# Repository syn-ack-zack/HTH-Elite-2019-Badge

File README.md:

# Hackers Teaching Hackers 2019 Badge
This repository contains the hardware and software source code to fabrciate the HTH 2019 Badge. Details on the use and flashing of the badge can be found below. 

## Badge Hardware Specs
* ESP32
* Atmel 32u4
* 96×64 Graphic Full Color OLED Display
* 19x Mini NeoPixel RGB LEDs
* 4 tactile buttons
* 8 Mb Storage
* 1 2x3 "Shitty Add On" Connector
* Powered via 2 AA batteries or USB

## Badge Functions
* LoRa Arsenal
	* LoRa 915Mhz Tactile Button Chat
	* LoRa 915Mhz Web App Chatroom
* WiFi Tools
	* 802.11 channel activity monitor
	* Access point scanner / Open AP detector
	* Packet Monitor and Deauth sniffer
	* Can act as a client or access point (modify config.json via SPIFFS to update AP connection details)
	* Webserver (edit filesystem files, trigger payloads remotely)
	* NTP client
* HID Toolkit (Not Working)
	* An issue with the serial communication currently prevents the ESP32 from controlling the Atmega. 
	* Any HID functionality must be standalone and flashed to the Atmega.
	* This repo will be updated as any changes occur.
	
* LED patterns and OLED graphics
* Misc. extras

## Usage Instructions
### Power Switch
In order to turn on the device, it must be powered via 2 AA batteries or USB. The main power switch is located in the center.

### Buttons / UI

Up and Down is on the left side of the OLED, and Left and Right is on the right side of the OLED.

In order to go into a menu or run a program, click the right button. To exit most applications, click the left button. Some programs like the snake game require all 4 buttons so there is no way to clean exit, a power cycle is needed. 

### HTH NET (LoRa 915Mhz)
This badge contains an SX1278 LoRa transceiver which allows for long range low bandwidth communication using the LoRa protocol over 915Mhz. Each badge is capable of receiving and sending messages using this frequency by utilizing the HTH NET feature of the badge. 

Once you start the chat it will display any received message on the screen. Follow the on screen prompts to type out and send messages. The '~' is used as a delimiter to signify the end of a typed message. 

Alternatively you can utililze the Webserver by first starting up the Access Point at `WiFi Server Tools -> AP Start`. Connect to this network and then start up the Webserver at `WiFi Server Tools -> Webserver Start`. Navigate to the indicated IP, http://10.0.1.5/ to access the web app. HTH Net can be utilized here to have a more convenient interface to send and recieve LoRa messages. 

### Webserver
Navigate to WiFi Server Tools -> Webserver Start. You can access the webserver if running an AP or if connected. The pages are protected through basic authentication, username and password generated dynamically and is provided on the screen.

A SPIFFS Editor can be used to edit the flash filesystem on the badge. This is useful to modify config files which are used in several instances. For instance, to have your badge connect to another wireless network, you configure the ESSID and Password in `config.json`. 

### Bling
There are 40+ LED patterns included. You can also trigger each type of pattern individually. 

## Configuration / Customization
### Settings menu in OLED UI
There are individual settings for OLED and LED brightness. Region setting is related to WiFi channel scanning.

### JSON configuration files
There are 4 different json files in SPIFFS. There are a couple ways to edit these files and get them loaded on the badge, but the easiest is through the webserver.
1. config.json = Main device configuration. Includes parameters such as LED and OLED brightness settings, ssid/password if connecting to a wireless client network, region information, and google auth HMAC. 
2. lin.json / win.json = Configuration files for the Linux and Windows KB/M payloads. 
3. static.json = Configuration file for the stored static strings. 

## Compiling Instructions
These instructions will get you a copy of the project up and running on your local machine.
### Prerequisites
What things you need to install the software and how to install them
```
1. Arduino / compiler
2. SparkFun Pro Micro v3 com driver
https://learn.sparkfun.com/tutorials/pro-micro--fio-v3-hookup-guide/installing-windows
https://learn.sparkfun.com/tutorials/pro-micro--fio-v3-hookup-guide/installing-mac--linux
3. Libraries
  https://raw.githubusercontent.com/sparkfun/Arduino_Boards/master/IDE_Board_Manager/package_sparkfun_index.json
  https://github.com/adafruit/Adafruit_NeoPixel
  https://github.com/adafruit/Adafruit-GFX-Library
  https://github.com/adafruit/Adafruit_CircuitPlayground
  https://github.com/kitesurfer1404/WS2812FX
  https://github.com/me-no-dev/ESPAsyncWebServer
  https://github.com/me-no-dev/AsyncTCP
  https://github.com/bblanchon/ArduinoJson
  https://github.com/me-no-dev/arduino-esp32fs-plugin
  https://github.com/sandeepmistry/arduino-LoRa
  Manually copy the SSD_13XX and qMenuSystem folders to Arduino libraries folder. We included a snapshot of the other libraries used in case newer versions break our code.
4. 3.3v FTDI serial cable
5. Hackers Teaching Hackers 2019 Badge
```
### Compiling / Flashing Atmel Code
* Set the board to SparkFun Pro Micro
* Set the processor as ATmega32u4 3.3v and NOT the 5v one

### Compiling / Flashing ESP Code
* Set the board to SparkFun ESP32 Thing

#### Programming through FTDI port 
To interface with the ESP32 over FTDI serial, you will need a FTDI USB adapter. These can be found online or at some retailers like MicroCenter. [FTDI Adapter on Amazon](https://www.amazon.com/HiLetgo-FT232RL-Converter-Adapter-Breakout/dp/B00IJXZQ7C/ref=pd_lpo_sbs_147_t_1?_encoding=UTF8&psc=1&refRID=TW098QMMC5YX7B7DFNS5)

1. Flash the atmel with the 'atmel-esp32ftdi-pin7' code first via the USB connection. this will toggle pin 7 and the rx/tx switch to change the serial port communiction to the FTDI port. 
2. Connect FTDI cable to the board while holding the left button down (which is on the right side, top button)
3. Upload code.
4. You can optionally flash the 'atmel-km-relay' code back to the atmel. Most serial functionality isn't working correctly at this time, however the mouse jiggler feature is configured to work when plugged in. Note that you may need to reset the the atmel by shorting GND to [Pin 13](https://www.arduino.cc/en/Hacking/PinMapping32u4) before succesfully reflashing. 

#### Programming through USB port / Atmel
Pass through programming doesn't work at the time of writing. Communication is passed through, but something is holding up the ESP32 from fully going into the programming mode

### Uploading SPIFFS files
The keyboard/mouse payloads, configuration files, webserver files are all files that are loaded into a special section in storage marked as SPIFFS. While still having pin 7 set to allow for the FTDI connection, use the 'ESP32 Sketch Data Upload' function in the tools menu. This will compress and compile all the files in the 'data' folder, and upload it. 

## Authors / Contributors
* **@syn-ack-zack**

## Acknowledgments
* Thanks to all contributes and maintainers of any codebase which was used or referenced. 
* Special thanks to Hacker Warehouse and Garret Gee for the work on their [DC26 badge](https://github.com/hackerwarehouse/HW-DC26-Badge). Much of the materials around the core components (esp32 / atmega34u ) was referenced from Hacker Warehouse's open sourced badge.

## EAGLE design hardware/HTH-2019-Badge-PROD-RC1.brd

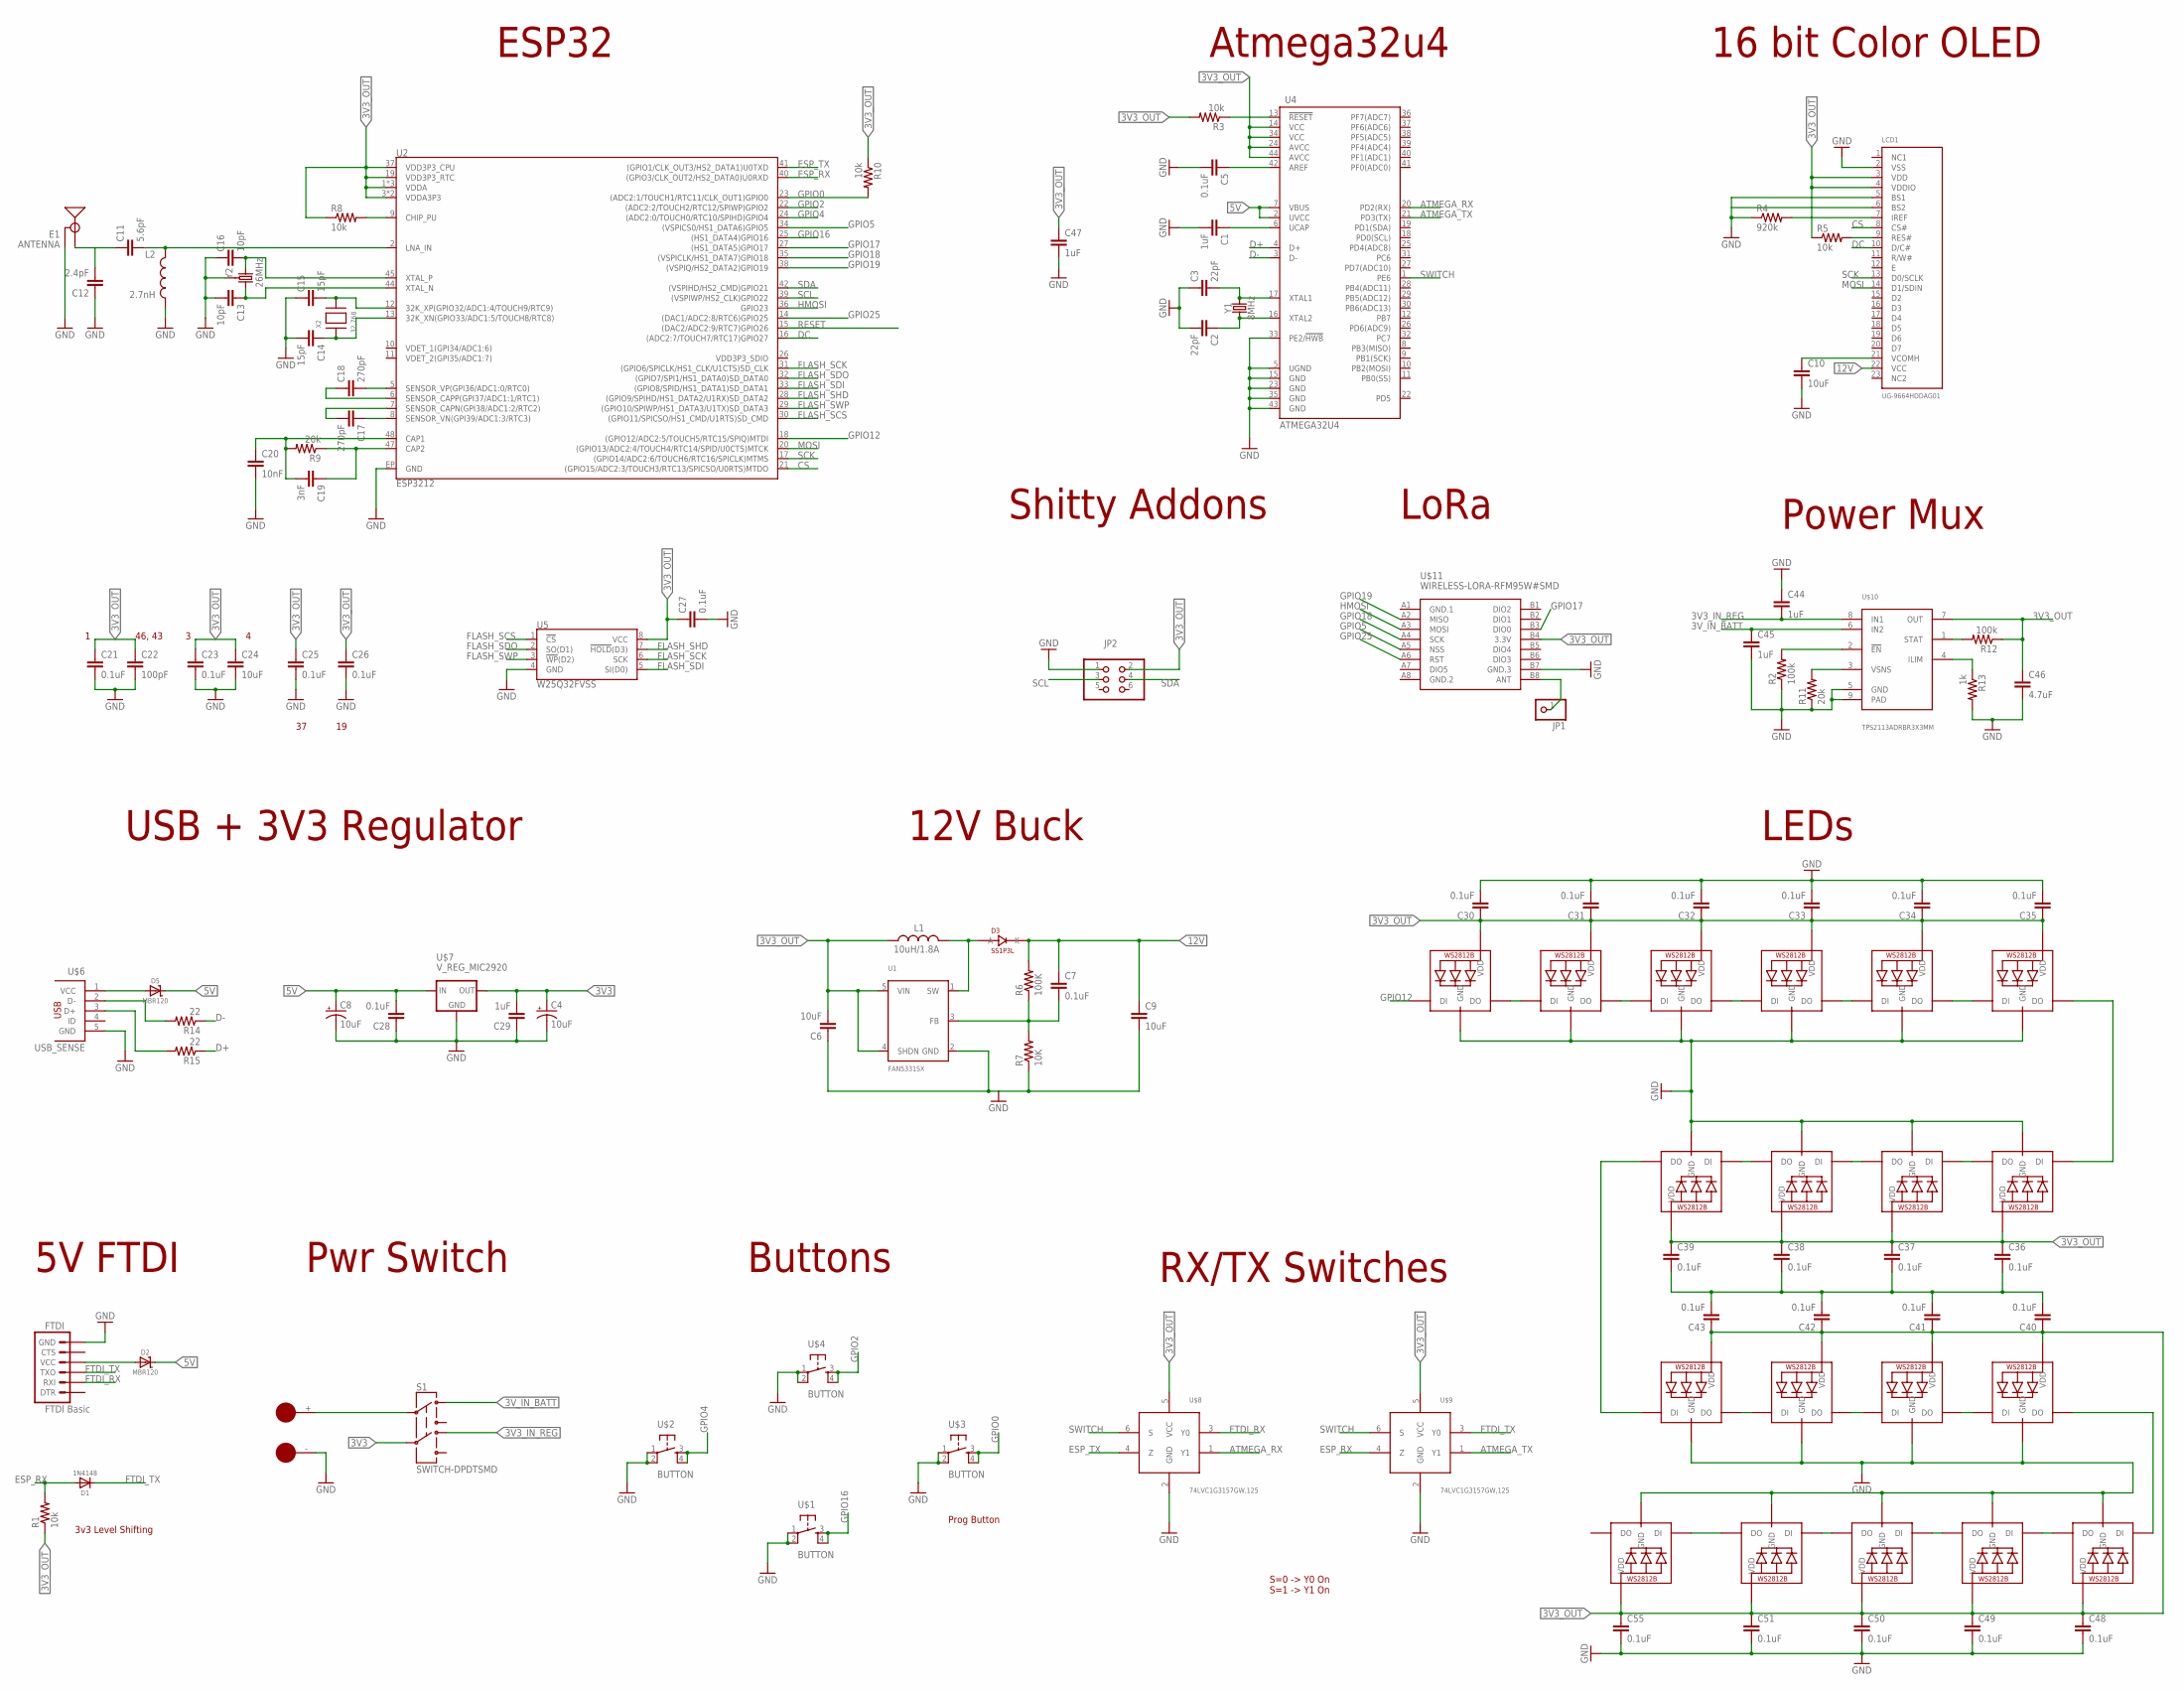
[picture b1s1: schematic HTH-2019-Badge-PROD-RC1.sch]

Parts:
C1, C29, C44, C45, C47: 1uF; CAP0603
C2, C3: 22pF; CAP0603
C4, C8: 10uF; EIA3216
C5, C7, C21, C23, C25, C26, C27, C28, C30, C31, C32, C33, C34, C35, C36, C37, C38, C39, C40, C41, C42, C43, C48, C49, C50, C51, C55: 0.1uF; CAP0603
C6, C9, C10, C24: 10uF; CAP0603
C11: 5.6pF; CAP0603
C12: 2.4pF; CAP0603
C13, C16: 10pF; CAP0603
C14, C15: 15pF; CAP0603
C17, C18: 270pF; CAP0603
C19: 3nF; CAP0603
C20: 10nF; CAP0603
C22: 100pF; CAP0603
C46: 4.7uF; CAP0603
D1: 1N4148; SOD-323
D2, D5: MBR120; SOD-123
D3: SS1P3L; DO220AAL
E1: ANTENNA; TRACE_ANTENNA_2.4GHZ_25.7MM_TUNED
FTDI: FTDI Basic; 1X06
JP1: PINHD-1X1; 1X01
JP2: PINHD-2X3; 2X03
L1: 10uH/1.8A; SRU5028
L2: 2.7nH; 0603
LCD1: UG-9664HDDAG01; UG-9664HDDAG01_WRAPAROUND
LED1, LED2, LED3, LED4, LED5, LED6, LED7, LED8, LED9, LED10, LED11, LED12, LED13, LED14, LED15, LED16, LED17, LED18, LED19: WS2812B3535; LED3535
R1, R3, R5, R8, R10: 10k; RES-0603
R2, R12: 100k; RES-0603
R4: 920k; RES-0603
R6: 100K; RES-0603
R7: 10K; RES-0603
R9, R11: 20k; RES-0603
R13: 1k; RES-0603
R14, R15: 22; RES-0603
S1: SWITCH-DPDTSMD; AYZ0202
U1: FAN5331SX; SOT23-5
U2: ESP3212; QFN48-0.4MM
U4: ATMEGA32U4; QFN-44-NOPAD_1:1-OUTFAKES
U5: W25Q32FVSS; SOIC-8
U$1, U$2, U$3, U$4: BUTTON
U$5: BAT_HOLD; AA
U$6: USB_SENSE; USB-MICRO-TH-SUPPORT
U$7: V_REG_MIC2920; SOT223
U$8, U$9: 74LVC1G3157GW,125; SOT-363
U$10: TPS2113ADRBR3X3MM; 8-VDFN
U$11: WIRELESS-LORA-RFM95W#SMD
X2: 32.768; XTAL3215
Y1: 8MHz; CRYSTAL-SMD-5X3.2-4PAD
Y2: 26MHz; CRYSTAL-SMD-3.2X2.5

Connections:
3V3: C4.A (+), C29.2, S1.5, U$7.3 (OUT)
3V3_IN_REG: C44.2, S1.4, U$10.8 (IN1)
3V3_OUT: C6.2, C21.1, C22.1, C23.1, C24.1, C25.1, C26.1, C27.1, C30.1, C31.1, C32.1, C33.1, C34.1, C35.1, C36.1, C37.1, C38.1, C39.1, C40.1, C41.1, C42.1, C43.1, C46.1, C47.1, C48.1, C49.1, C50.1, C51.1, C55.1, JP2.2, L1.1, LCD1.3 (VDD), LCD1.4 (VDDIO), LED1.2 (VDD), LED2.2 (VDD), LED3.2 (VDD), LED4.2 (VDD), LED5.2 (VDD), LED6.2 (VDD), LED7.2 (VDD), LED8.2 (VDD), LED9.2 (VDD), LED10.2 (VDD), LED11.2 (VDD), LED12.2 (VDD), LED13.2 (VDD), LED14.2 (VDD), LED15.2 (VDD), LED16.2 (VDD), LED17.2 (VDD), LED18.2 (VDD), LED19.2 (VDD), R1.1, R3.2, R5.1, R8.1, R10.1, R12.1, U1.4 (SHDN), U1.5 (VIN), U2.1 (VDDA), U2.3 (VDDA3P3), U2.4 (VDDA3P3), U2.19 (VDD3P3_RTC), U2.37 (VDD3P3_CPU), U2.43 (VDDA), U2.46 (VDDA), U4.14 (VCC), U4.24 (AVCC), U4.34 (VCC), U4.44 (AVCC), U5.8 (VCC), U$8.5 (VCC), U$9.5 (VCC), U$10.7 (OUT), U$11.B4 (3.3V)
3V_IN_BATT: C45.1, S1.1, U$10.6 (IN2)
5V: C8.A (+), C28.2, D2.C, D5.C, U4.2 (UVCC), U4.7 (VBUS), U$7.1 (IN)
12V: C7.1, C9.1, D3.P$1 (K), LCD1.22 (VCC), R6.2
ATMEGA_RX: U4.20 (PD2(RX)), U$8.1 (Y1)
ATMEGA_TX: U4.21 (PD3(TX)), U$9.1 (Y1)
CS: LCD1.8 (CS#), U2.21 ((GPIO15/ADC2:3/TOUCH3/RTC13/SPICSO/U0RT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)
D+: R15.1, U4.4 (D+)
D-: R14.1, U4.3 (D-)
DC: LCD1.10 (D/C#), U2.16 ((ADC2:7/TOUCH7/RTC17)GPIO27)
ESP_RX: D1.A, R1.2, U2.40 ((GPIO3/CLK_OUT2/HS2_DATA0)U0RXD), U$9.4 (Z)
ESP_TX: U2.41 ((GPIO1/CLK_OUT3/HS2_DATA1)U0TXD), U$8.4 (Z)
FLASH_SCK: U2.31 ((GPIO6/SPICLK/HS1_CLK/U1CTS)SD_CLK), U5.6 (SCK)
FLASH_SCS: U2.30 ((GPIO11/SPICSO/HS1_CMD/U1RTS)SD_CMD), U5.1 (!CS!)
FLASH_SDI: U2.33 ((GPIO8/SPID/HS1_DATA1)SD_DATA1), U5.5 (SI(D0))
FLASH_SDO: U2.32 ((GPIO7/SPI1/HS1_DATA0)SD_DATA0), U5.2 (SO(D1))
FLASH_SHD: U2.28 ((GPIO9/SPIHD/HS1_DATA2/U1RX)SD_DATA2), U5.7 (!HOLD!(D3))
FLASH_SWP: U2.29 ((GPIO10/SPIWP/HS1_DATA3/U1TX)SD_DATA3), U5.3 (!WP!(D2))
FTDI_RX: FTDI.2 (RXI), U$8.3 (Y0)
FTDI_TX: D1.C, FTDI.3 (TXO), U$9.3 (Y0)
GND: C1.2, C2.2, C3.1, C4.C (-), C5.2, C6.1, C8.C (-), C9.2, C10.2, C12.1, C13.2, C14.2, C15.1, C16.1, C20.2, C21.2, C22.2, C23.2, C24.2, C25.2, C26.2, C27.2, C28.1, C29.1, C30.2, C31.2, C32.2, C33.2, C34.2, C35.2, C44.1, C45.2, C46.2, C47.2, C48.2, C49.2, C50.2, C51.2, C55.2, E1.GND, E1.GND2 (GND), FTDI.6 (GND), JP2.1, L2.2, LCD1.2 (VSS), LCD1.5 (BS1), LED1.4 (GND), LED2.4 (GND), LED3.4 (GND), LED4.4 (GND), LED5.4 (GND), LED6.4 (GND), LED7.4 (GND), LED8.4 (GND), LED9.4 (GND), LED10.4 (GND), LED11.4 (GND), LED12.4 (GND), LED13.4 (GND), LED14.4 (GND), LED15.4 (GND), LED16.4 (GND), LED17.4 (GND), LED18.4 (GND), LED19.4 (GND), R2.1, R4.1, R7.1, R11.1, R13.2, U1.2 (GND), U2.EP (GND), U4.5 (UGND), U4.15 (GND), U4.23 (GND), U4.33 (PE2/!HWB), U4.35 (GND), U4.43 (GND), U5.4 (GND), U$1.1, U$1.2, U$2.1, U$2.2, U$3.1, U$3.2, U$4.1, U$4.2, U$5.-, U$6.5 (GND), U$7.2 (GND), U$7.4 (GND), U$8.2 (GND), U$9.2 (GND), U$10.5 (GND), U$10.9 (PAD), U$11.B7 (GND.3), Y2.2 (GND), Y2.4 (GND)
GND.1: U$11.A1 (GND.1)
GND.2: U$11.A8 (GND.2)
GPIO0: R10.2, U2.23 ((ADC2:1/TOUCH1/RTC11/CLK_OUT1)GPIO0), U$3.3, U$3.4
GPIO2: U2.22 ((ADC2:2/TOUCH2/RTC12/SPIWP)GPIO2), U$4.3, U$4.4
GPIO4: U2.24 ((ADC2:0/TOUCH0/RTC10/SPIHD)GPIO4), U$2.3, U$2.4
GPIO5: U2.34 ((VSPICS0/HS1_DATA6)GPIO5), U$11.A5 (NSS)
GPIO12: LED5.1 (DI), U2.18 ((GPIO12/ADC2:5/TOUCH5/RTC15/SPIQ)MTDI)
GPIO16: U2.25 ((HS1_DATA4)GPIO16), U$1.3, U$1.4
GPIO17: U2.27 ((HS1_DATA5)GPIO17), U$11.B3 (DIO0)
GPIO18: U2.35 ((VSPICLK/HS1_DATA7)GPIO18), U$11.A4 (SCK)
GPIO19: U2.38 ((VSPIQ/HS2_DATA2)GPIO19), U$11.A2 (MISO)
GPIO25: U2.14 ((DAC1/ADC2:8/RTC6)GPIO25), U$11.A6 (RST)
HMOSI: U2.36 (GPIO23), U$11.A3 (MOSI)
MOSI: LCD1.14 (D1/SDIN), U2.20 ((GPIO13/ADC2:4/TOUCH4/RTC14/SPID/U0CTS)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)
unnamed: C3.2, U4.17 (XTAL1), Y1.3 (2)
unnamed: R3.1, U4.13 (!RESET)
unnamed: C1.1, U4.6 (UCAP)
unnamed: C5.1, U4.42 (AREF)
unnamed: R14.2, U$6.2 (D-)
unnamed: C10.1, LCD1.21 (VCOMH)
unnamed: D3.P$2 (A), L1.2, U1.1 (SW)
unnamed: C2.1, U4.16 (XTAL2), Y1.1
unnamed: LED1.1 (DI), LED14.3 (DO)
unnamed: C7.2, R6.1, R7.2, U1.3 (FB)
unnamed: LCD1.7 (IREF), R4.2
unnamed: S1.2, U$5.+
unnamed: R8.2, U2.9 (CHIP_PU)
unnamed: C16.2, U2.45 (XTAL_P), Y2.1
unnamed: C11.1, C12.2, E1.ANT (SIGNAL)
unnamed: LED1.3 (DO), LED2.1 (DI)
unnamed: D2.A, FTDI.4 (VCC)
unnamed: LED5.3 (DO), LED6.1 (DI)
unnamed: C19.2, C20.1, R9.2, U2.48 (CAP1)
unnamed: C11.2, L2.1, U2.2 (LNA_IN)
unnamed: C13.1, U2.44 (XTAL_N), Y2.3 (2)
unnamed: C19.1, R9.1, U2.47 (CAP2)
unnamed: C15.2, U2.12 (32K_XP(GPIO32/ADC1:4/TOUCH9/RTC9)), X2.P$2
unnamed: C14.1, U2.13 (32K_XN(GPIO33/ADC1:5/TOUCH8/RTC8)), X2.P$1
unnamed: C18.2, U2.5 (SENSOR_VP(GPI36/ADC1:0/RTC0))
unnamed: C18.1, U2.6 (SENSOR_CAPP(GPI37/ADC1:1/RTC1))
unnamed: C17.2, U2.7 (SENSOR_CAPN(GPI38/ADC1:2/RTC2))
unnamed: C17.1, U2.8 (SENSOR_VN(GPI39/ADC1:3/RTC3))
unnamed: D5.A, U$6.1 (VCC)
unnamed: LED6.3 (DO), LED7.1 (DI)
unnamed: LED7.3 (DO), LED8.1 (DI)
unnamed: LED8.3 (DO), LED9.1 (DI)
unnamed: LED9.3 (DO), LED11.1 (DI)
unnamed: LED11.3 (DO), LED13.1 (DI)
unnamed: LED10.1 (DI), LED13.3 (DO)
unnamed: LED10.3 (DO), LED12.1 (DI)
unnamed: LED12.3 (DO), LED14.1 (DI)
unnamed: LED2.3 (DO), LED3.1 (DI)
unnamed: LED3.3 (DO), LED4.1 (DI)
unnamed: LED15.3 (DO), LED16.1 (DI)
unnamed: LED16.3 (DO), LED17.1 (DI)
unnamed: R15.2, U$6.3 (D+)
unnamed: LED17.3 (DO), LED18.1 (DI)
unnamed: JP1.1, U$11.B8 (ANT)
unnamed: C36.2, C37.2, C38.2, C39.2, C40.2, C41.2, C42.2, C43.2
unnamed: LED4.3 (DO), LED15.1 (DI)
unnamed: LED18.3 (DO), LED19.1 (DI)
unnamed: R2.2, U$10.2 (!EN)
unnamed: R11.2, U$10.3 (VSNS)
unnamed: R12.2, U$10.1 (STAT)
unnamed: R13.1, U$10.4 (ILIM)
RESET: LCD1.9 (RES#), R5.2, U2.15 ((DAC2/ADC2:9/RTC7)GPIO26)
SCK: LCD1.13 (D0/SCLK), U2.17 ((GPIO14/ADC2:6/TOUCH6/RTC16/SPICLK)MTMS)
SCL: JP2.3, U2.39 ((VSPIWP/HS2_CLK)GPIO22)
SDA: JP2.4, U2.42 ((VSPIHD/HS2_CMD)GPIO21)
SWITCH: U4.1 (PE6), U$8.6 (S), U$9.6 (S)

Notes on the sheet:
ESP32
Atmega32u4
16 bit Color OLED
USB + 3V3 Regulator
5V FTDI
12V Buck
Pwr Switch
Buttons
Shitty Addons
LEDs
S=0 -> Y0 On S=1 -> Y1 On
RX/TX Switches
46, 43
Power Mux
3v3 Level Shifting
Prog Button
LoRa

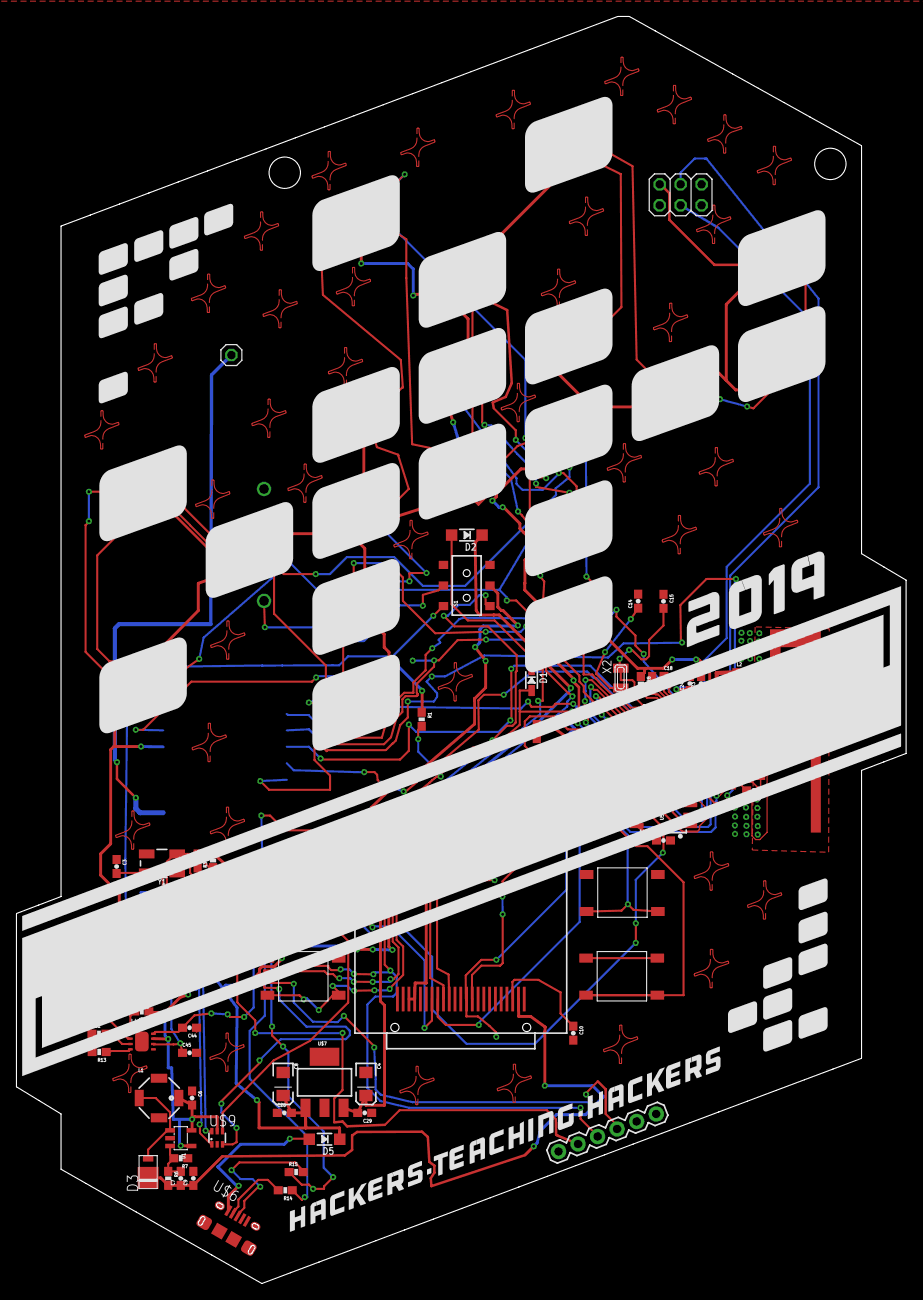
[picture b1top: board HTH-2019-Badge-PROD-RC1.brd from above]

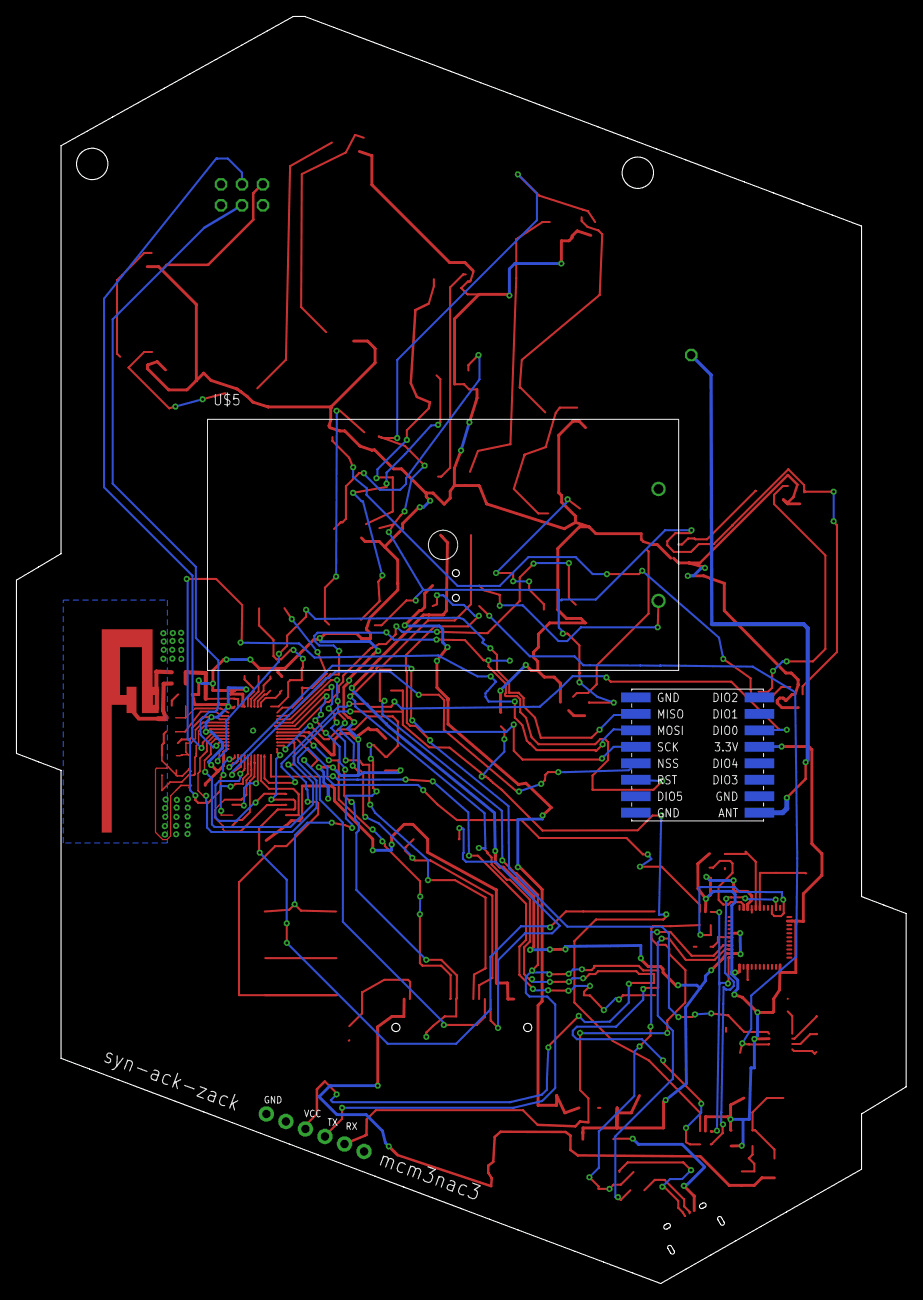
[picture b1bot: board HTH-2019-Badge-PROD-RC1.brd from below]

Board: 2 copper layers, 108.0 x 153.8 mm, 116 parts (2 on the bottom side), 91 nets.

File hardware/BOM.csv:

,,Note,part number ,Quantity,Description,Alternative Part Number,Reference Designator
,,,CL10C220JB8NNNC,2,22PF 50V NP0 0603 Capacitor,C1608C0G1H220G080AA,"C2, C3"
,,5-7work days,F931C106MAAAJ6,2,10uf Tantalum Capacitor 1206 16V 20%,F931C106MAA,"C4, C8"
,,,C1608X6S1C475K080AC,1,4.7UF 16V X5R 0603,,C46
,,,CL10A106MA8NRNC,4,10uF 25V 20% 0603 Capacitor,,"C6, C9, C10, C24"
,,TME MOQ:100pcs 5-7work days,CL10B103KC8NNNC,1,.01uf/10nf 100V 0603 10% Capacitor,,C20
,,,CC0603MRY5V6BB105,5,1uf 16V 10% 0603 Capacitor,CL10A105KO8NNNC,"C1, C29, C44, C45, C47"
,,5-7work days,06033C104KAZ2A,27,0.1uf 25V 10% 0603 Capacitor,CL10B104KA8NNNC,"C5, C7, C21, C23, C25, C26, C27, C28, C30, C31, C32, C33, C34, C35, C36, C37, C38, C39, C40, C41, C42, C43, C48, C49, C50, C51, C55"
,,,VJ0603Y332KXJCW1BC,1,3.3nf 16V 10% 0603 Capacitor,,C19
,,5-7work days,GRM1885C2A101JA01D,1,100pf/0.1nf 100V 0603 Capacitor,,C22
,,,C1608C0G1H100C080AA,2,"10pF 脗卤0.25pF 50V Ceramic Capacitor C0G, NP0 0603",,"C13, C16"
,,,CL10C5R6DB8NNNC,1,5.6pF Ceramic Capacitor +-0.5pF 50V 0603,,C11
,,,CC0603JRNPO9BN150,2,CAP CER 15PF 50V C0G/NPO 0603,,"C14, C15"
,,,CL10C2R4CB8NNNC,1,CAP CER 2.4PF 50V C0G/NP0 0603,,C12
,,,CL10B271KB8NNNC,2,CAP CER 270PF 50V X7R 0603,,"C17, C18"
,,,SS1P3L-M3/84A,1,SS1P3L Schottky Diode 30V 1A,,D3
,,,B140HW-7,2,DIODE SCHOTTKY 40V 1A SOD123,,"D2, D5"
,,5-7work days,1N914BWS,1,Diode Standard 75V 150mA SOD-323F,,D1
,,MOQ：1500pcs  1500pcs / bag,SK6812MINI,19,3535 RGB Addressable LED,,"LED1, LED2, LED3, LED4, LED5, LED6, LED7, LED8, LED9, LED10, LED11, LED12, LED13, LED14, LED15, LED16, LED17, LED18, LED19"
,,7-10work days,AYZ0202AGRLC,1,DPDT Slide Switch (On/Off) SMT,,S1
,,7-10work days,TL3301NF100QG,4,Black Momentary Push Button - SMD,,"U$1, U$2, U$3, U$4"
,,,10118194-0001LF,1,USB Micro-B RECPT SMD Connector,,U$6
,,5-7work days,BC2AAPC,1,Battery Holder 2-AA TH,,U$5
,,,ATMEGA32U4-MU,1,ATMEGA32U4-MU Microcontroller QFN,,U4
,,5-7work days,FAN5331SX,1,LED Driver Regulator 1A SOT23-5,,U1
,,5-7work days,MIC5209-3.3YS-TR,1,IC REG LINEAR 3.3V 500MA SOT223,,U$7
,,,"74LVC1G3157GW,125",2,IC MUX/DEMUX 2X1 6TSSOP,,"U$8, U$9"
,,ESP32-D0WDQ6 QFN 6*6,ESP3212,1,ESP3212,,U2
,,5-7work days,TPS2113ADRBR,1,IC OR CTRLR SRC SELECT 8SON,,U$10
,,5-7work days,W25Q64JVSSIM TR,1,IC FLASH 64MBIT SPI 8SOIC W25Q64JVSSIM TR,,U5
,,5-7work days,SRU5018-100Y,1,10 uH Inductor 1.8A 5028,,L1
,,,HK16082N7S-T,1,FIXED IND 2.7NH 300MA 100 MOHM,,L2
,,,UG-9664HDDAG01,1,0.95 inch (96 x 64) Pixel Full Color Passive OLED LCD,,LCD1
,,,RC0603JR-07100KL,3,100K Resistor 0603 1/10W 5%,,"R2, R6, R12"
,,,ERJ-3GEYJ102V,1,1K OHM 5% 1/10W 0603 Resistor,RC0603JR-071KL,R13
,,,RC0603JR-0710KL,6,10K Resisitor 0603 1/10W 5%,,"R1, R3, R5, R7, R8, R10"
,,,RC0603FR-071ML,1,1M Resistor 0603 1/10W 1%,,R4
,,,RC0603JR-0722RL,2,22 ohm Resistor 0603 1/10W 5%,,"R14, R15"
,,,RC0603FR-0720KL,2,RES SMD 20K OHM 1% 1/10W 0603,,"R9, R11"
,,5-7work days,ABM3B-8.000MHZ-B2-T,1,8.0 MHz Crystal 5 mm x 3.2 mm,,Y1
,,5-7work days,ABS07-32.768KHZ-T,1,32.768 KHz Crystal FC-135 32.7680KA-A3,FC-135 32.7680KA-A3,X2
,,5-7work days,TSX-3225 26.0000MF09Z-AC0,1,Crystal 26MHz 3.2 x 2.5,,Y2
,,,,,,,
,,,,,,,
,,,,,,,
0.5KG,,,,,,,

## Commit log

2019-07-08 Initial Public Push
2019-10-31 Bump ws in /libraries/ArduinoHttpClient/examples/node_test_server
    Bumps [ws](https://github.com/websockets/ws) from 1.1.5 to 7.2.0.
    - [Release notes](https://github.com/websockets/ws/releases)
    - [Commits](https://github.com/websockets/ws/compare/1.1.5...7.2.0)

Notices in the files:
parts and their libraries:
SparkFun-DigitalIC: Licensing: CC v3.0 Share-Alike You are welcome to use this library for commercial purposes.
Jaycon OPL Capacitors: Licensing: Creative Commons ShareAlike 4.0 International - https://creativecommons.org/licenses/by-sa/4.0
